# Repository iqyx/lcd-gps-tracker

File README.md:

GPS tracker with a simple LCD interface
==================================================

After much negative experience with Android GPS tracking (battery usage, bad
reception) I decided to build my own dedicated GPS tracker despite the fact that
multiple similar devices are readily available on the market.

Selected components
----------------------

  * Quectel L70B GPS receiver module with low power tracking function. They claim
    1.4mA tracking current draw under static conditions. We will see.
  * STM32F401 microcontroller in a QFN48 package, low power run mode
  * EA DOGS 102x64px graphic LCD module with low power consumption (0.25mA)
  * USB connections for charging and downloading data
  * SPI serial flash for data storage (8Mbit/16Mbt)
  * 600mAh 3.7V LiPo cell

Battery and memory size
----------------------------

The goal is 5mA current draw which should be enough to provide nearly 4 days of
continuous logging using the mentioned 600mAh LiPo cell. Such cells are
available in local stores or on eBay.

The following items will be saved:

  * 32 bits for the actual time
  * 32 bits for latitude
  * 32 bits for longitude
  * 16 bits for height
  * 16 bits reserved for header and other data

Which gives 16 bytes for a single point or 65536 points in a 1MB flash memory.
Considering 5 second logging interval (should be enough fir hiking), the flash
memory should suffice for 91 hours of logging, which is nearly 4 days.

Project status
------------------

As of 2016-02-06, basic requirements are determined and the schematic is ready.
Board layout is WIP.

Bill of materials
----------------------

TODO

Schematic and layout pictures
----------------------------------

[schematic](doc/schematic.png)

Prototype photos
-------------------

TODO

Resources
--------------

You can access the schematic/layout files and firmware at
[https://github.com/iqyx/lcd-gps-tracker](https://github.com/iqyx/lcd-gps-tracker)

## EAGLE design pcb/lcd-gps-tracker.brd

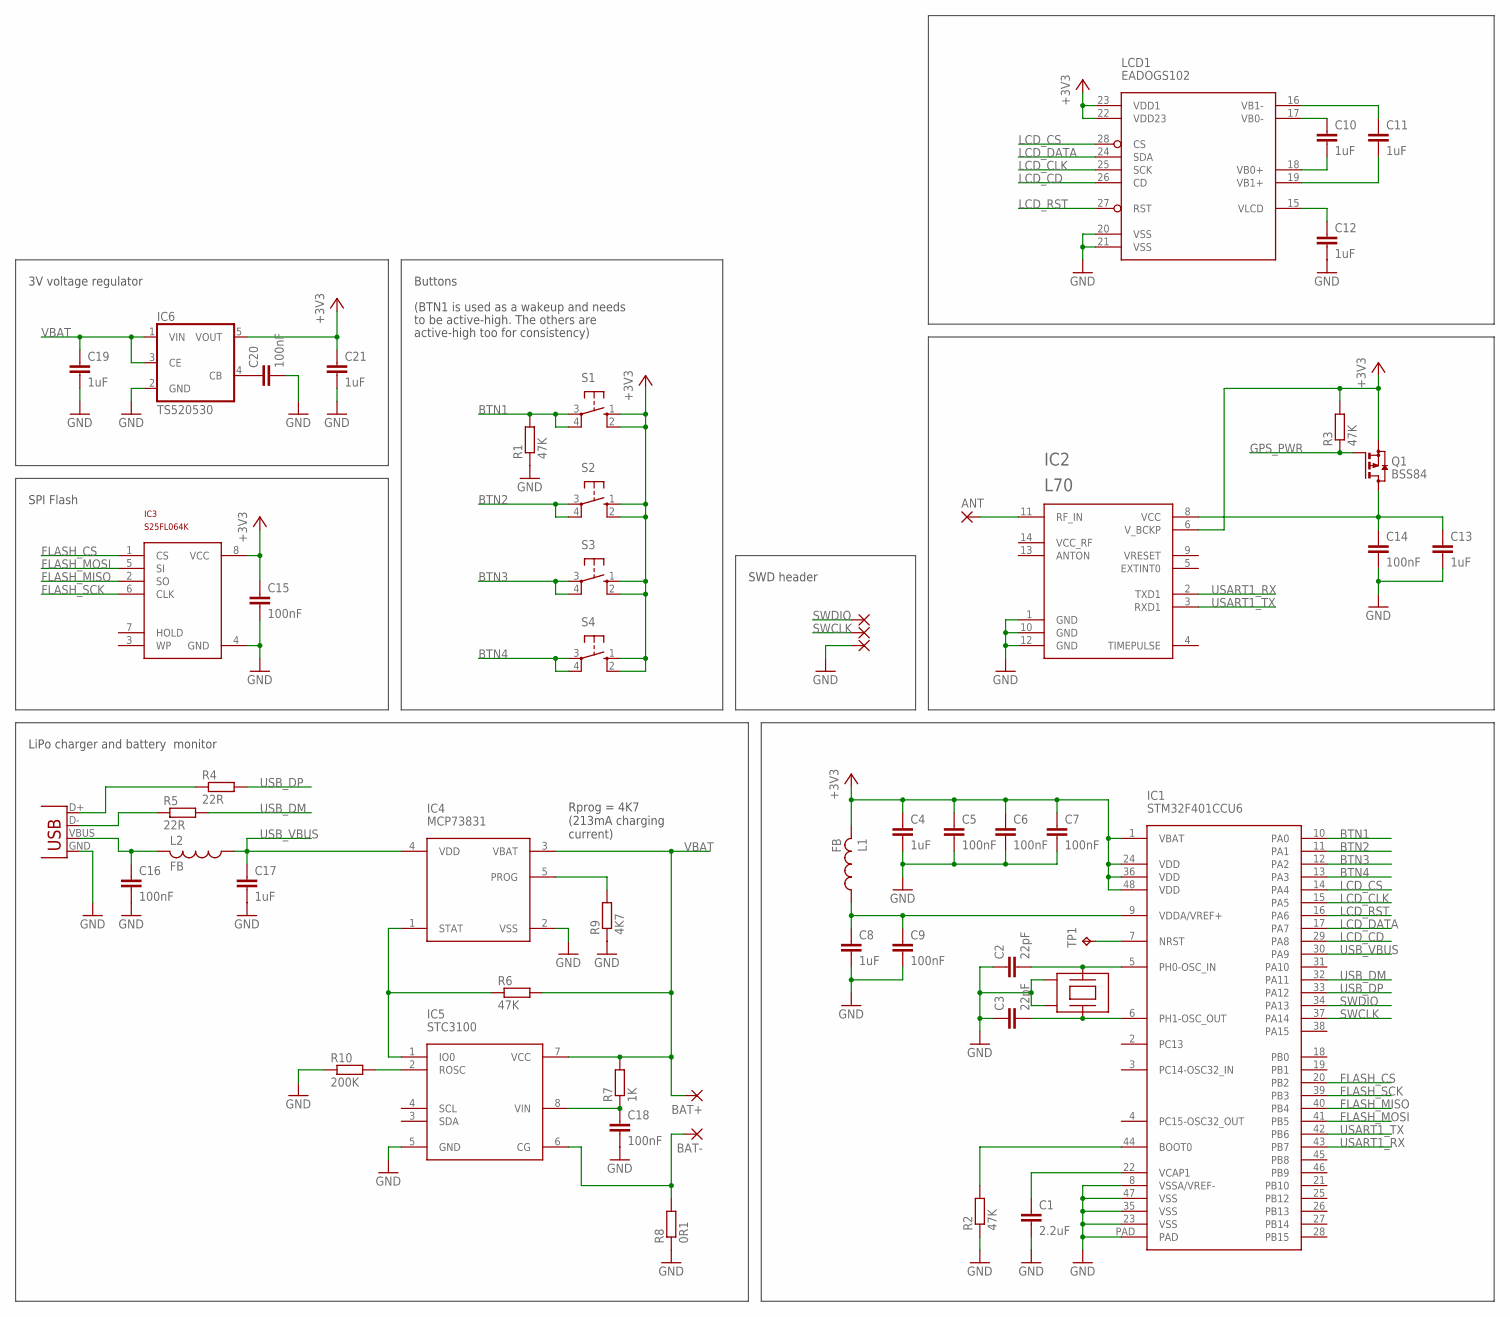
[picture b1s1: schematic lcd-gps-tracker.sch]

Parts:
ANT: 2,54/1,0
BAT+: SMD2; SMD1,27-2,54
BAT-: SMD2; SMD1,27-2,54
C1: 2.2uF; C0805
C2, C3: 22pF; C0603
C4, C8, C10, C11, C12, C13, C19, C21: 1uF; C0603
C5, C6, C7, C9, C14, C15, C16, C18, C20: 100nF; C0603
C17: 1uF; C0805
IC1: STM32F401CCU6; UFQFPN48
IC2: L70
IC3: S25FL064K; SO-08M
IC4: MCP73831; SOT23-5
IC5: STC3100; MSOP8
IC6: TS520530; SOT25
L1, L2: FB; L2012C
LCD1: EADOGS102; EADOGS
Q1: BSS84; SOT23
R1, R2, R3, R6: 47K; R0603
R4, R5: 22R; R0603
R7: 1K; R0603
R8: 0R1; R0805
R9: 4K7; R0603
R10: 200K; R0603
S1, S2, S3, S4: 10-XX; B3F-10XX
SWCLK: SMD2; SMD1,27-2,54
SWDIO: SMD2; SMD1,27-2,54
SWGND: SMD2; SMD1,27-2,54
TP1: TPB1,27; B1,27
U$1: XTAL-7M; XTAL_7M
X1: USB-MICROB

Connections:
+3V3: C4.1, C5.1, C6.1, C7.1, C15.1, C21.1, IC1.1 (VBAT), IC1.24 (VDD), IC1.36 (VDD), IC1.48 (VDD), IC2.6 (V_BCKP), IC3.8 (VCC), IC6.5 (VOUT), L1.2, LCD1.22 (VDD23), LCD1.23 (VDD1), Q1.2 (S), R3.2, S1.1 (S), S1.2 (S1), S2.1 (S), S2.2 (S1), S3.1 (S), S3.2 (S1), S4.1 (S), S4.2 (S1)
BTN1: IC1.10 (PA0), R1.2, S1.3, S1.4 (P1)
BTN2: IC1.11 (PA1), S2.3, S2.4 (P1)
BTN3: IC1.12 (PA2), S3.3, S3.4 (P1)
BTN4: IC1.13 (PA3), S4.3, S4.4 (P1)
FLASH_CS: IC1.20 (PB2), IC3.1 (CS)
FLASH_MISO: IC1.40 (PB4), IC3.2 (SO)
FLASH_MOSI: IC1.41 (PB5), IC3.5 (SI)
FLASH_SCK: IC1.39 (PB3), IC3.6 (CLK)
GND: C1.2, C2.1, C3.1, C4.2, C5.2, C6.2, C7.2, C8.2, C9.2, C12.2, C13.2, C14.2, C15.2, C16.2, C17.2, C18.2, C19.2, C20.2, C21.2, IC1.8 (VSSA/VREF-), IC1.23 (VSS), IC1.35 (VSS), IC1.47 (VSS), IC1.PAD, IC2.1 (GND), IC2.10 (GND), IC2.12 (GND), IC3.4 (GND), IC4.2 (VSS), IC5.5 (GND), IC6.2 (GND), LCD1.20 (VSS), LCD1.21 (VSS), R1.1, R2.1, R8.1, R9.1, R10.1, SWGND.1, U$1.2 (G1), U$1.4 (G2), X1.GND
GPS_PWR: Q1.1 (G), R3.1
LCD_CD: IC1.29 (PA8), LCD1.26 (CD)
LCD_CLK: IC1.15 (PA5), LCD1.25 (SCK)
LCD_CS: IC1.14 (PA4), LCD1.28 (CS)
LCD_DATA: IC1.17 (PA7), LCD1.24 (SDA)
LCD_RST: IC1.16 (PA6), LCD1.27 (RST)
unnamed: C16.1, L2.2, X1.VBUS
unnamed: R5.1, X1.D-
unnamed: C1.1, IC1.22 (VCAP1)
unnamed: IC1.44 (BOOT0), R2.2
unnamed: C2.2, IC1.5 (PH0-OSC_IN), U$1.1
unnamed: C3.2, IC1.6 (PH1-OSC_OUT), U$1.3 (2)
unnamed: IC1.7 (NRST), TP1.TP
unnamed: C12.1, LCD1.15 (VLCD)
unnamed: C10.2, LCD1.18 (VB0+)
unnamed: C8.1, C9.1, IC1.9 (VDDA/VREF+), L1.1
unnamed: C10.1, LCD1.17 (VB0-)
unnamed: C11.1, LCD1.16 (VB1-)
unnamed: C11.2, LCD1.19 (VB1+)
unnamed: C13.1, C14.1, IC2.8 (VCC), Q1.3 (D)
unnamed: ANT.1, IC2.11 (RF_IN)
unnamed: R4.1, X1.D+
unnamed: IC4.1 (STAT), IC5.1 (IO0), R6.1
unnamed: IC4.5 (PROG), R9.2
unnamed: C18.1, IC5.8 (VIN), R7.1
unnamed: BAT-.1, IC5.6 (CG), R8.2
unnamed: IC5.2 (ROSC), R10.2
unnamed: C20.1, IC6.4 (CB)
SWCLK: IC1.37 (PA14), SWCLK.1
SWDIO: IC1.34 (PA13), SWDIO.1
USART1_RX: IC1.43 (PB7), IC2.2 (TXD1)
USART1_TX: IC1.42 (PB6), IC2.3 (RXD1)
USB_DM: IC1.32 (PA11), R5.2
USB_DP: IC1.33 (PA12), R4.2
USB_VBUS: C17.1, IC1.30 (PA9), IC4.4 (VDD), L2.1
VBAT: BAT+.1, C19.1, IC4.3 (VBAT), IC5.7 (VCC), IC6.1 (VIN), IC6.3 (CE), R6.2, R7.2

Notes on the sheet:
SWD header
Buttons
(BTN1 is used as a wakeup and needs
to be active-high. The others are
active-high too for consistency)
3V voltage regulator
SPI Flash
Rprog = 4K7 (213mA charging current)
LiPo charger and battery monitor

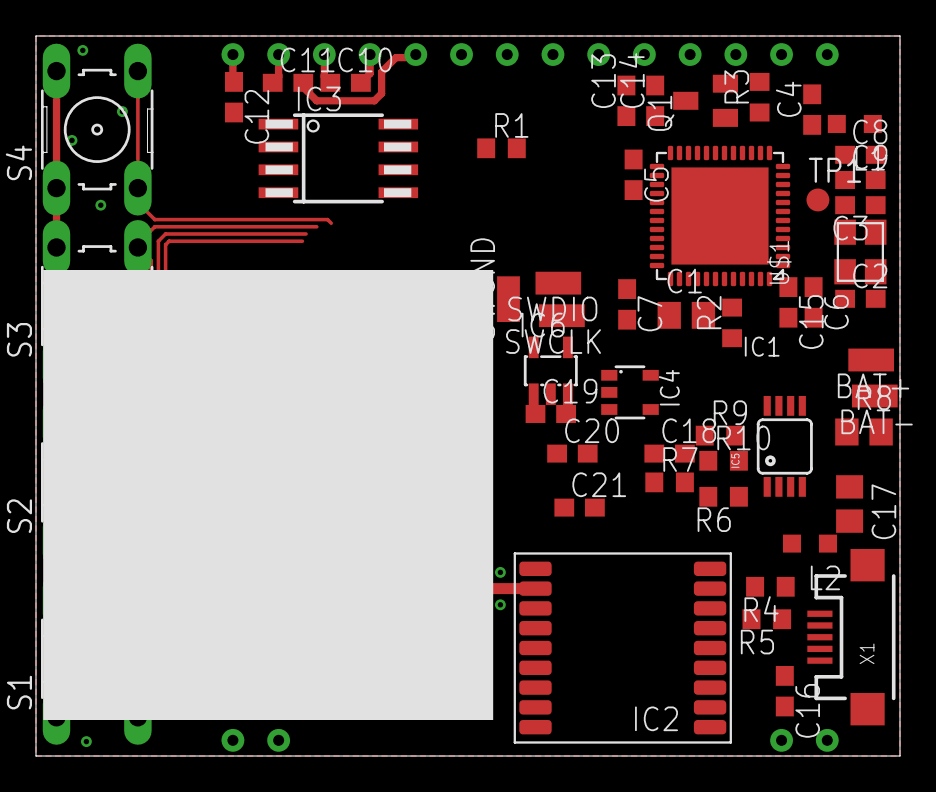
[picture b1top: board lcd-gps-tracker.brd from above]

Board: 2 copper layers, 48.0 x 40.0 mm, 54 parts (1 on the bottom side), 46 nets.

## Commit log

2016-02-06 Initial commit. Add basic project description
2016-02-06 Add schematic and layout files (first revision)
2016-02-06 Rename the project page file to README.md
2016-02-06 Add project status and schematic picture to README.md

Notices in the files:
parts and their libraries:
SparkFun: Licensing: CC v3.0 Share-Alike You are welcome to use this library for commercial purposes.
